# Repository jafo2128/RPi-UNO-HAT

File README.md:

# RPi-UNO-HAT
Raspberry Pi to Arduino/Genuino Shield Bridge.

## Shop
* [RPi-UNO-HAT](http://www.watterott.com/en/RPi-UNO-HAT)

## Features
* Atmel AVR ATmega328 with Arduino compatible Bootloader (optiboot)
* Raspberry Pi connected via I2C and UART (to the AVR through level-shifter)
* AVR-Programming via Raspberry Pi possible
* Shield connectors with Uno R3 layout
* Additional 3.3V LDO voltage regulator for Shields
* Optional 7-36V power input for Raspberry Pi and RPi-UNO-HAT (Murata OKI-78SR-5)

## Hardware and Software
* [Schematics + Layout](https://github.com/watterott/RPi-UNO-HAT/tree/master/hardware)
* [How to install the Arduino IDE on Raspberry Pi](https://github.com/watterott/RPi-UNO-HAT/blob/master/docu/Arduino.md)
* [How to control the RPi-UNO-HAT with Firmata](https://github.com/watterott/RPi-UNO-HAT/blob/master/docu/Firmata.md)
* [How to communicate with the RPi-UNO-HAT via I2C](https://github.com/watterott/RPi-UNO-HAT/blob/master/docu/I2CTest.md)
* [How to flash/update EEPROM on the RPi-UNO-HAT](https://github.com/watterott/RPi-UNO-HAT/blob/master/docu/EEPROM.md)
* [Nuage a Arduino Yún compatible device](http://www.arduino-hausautomation.de/nuage/)

Finally words from us Archivers and Developers.. 

##### Donate

People from time to time wish to donate a little money. Donating won't get you anything special, other than a warm feeling inside, and possibly urge me to produce more freely available material for interesting projects. You can donate via [PayPal](https://www.paypal.com), just click [donate](https://www.paypal.com/cgi-bin/webscr?cmd=_s-xclick&hosted_button_id=3PXVSLXFBS45E) button available below - it will redirect you to the secured PayPal page where you can provide donation amount (there is no minimal value). Any donations are apreciated greatly, and we thank you all in advance for your support along the ways..

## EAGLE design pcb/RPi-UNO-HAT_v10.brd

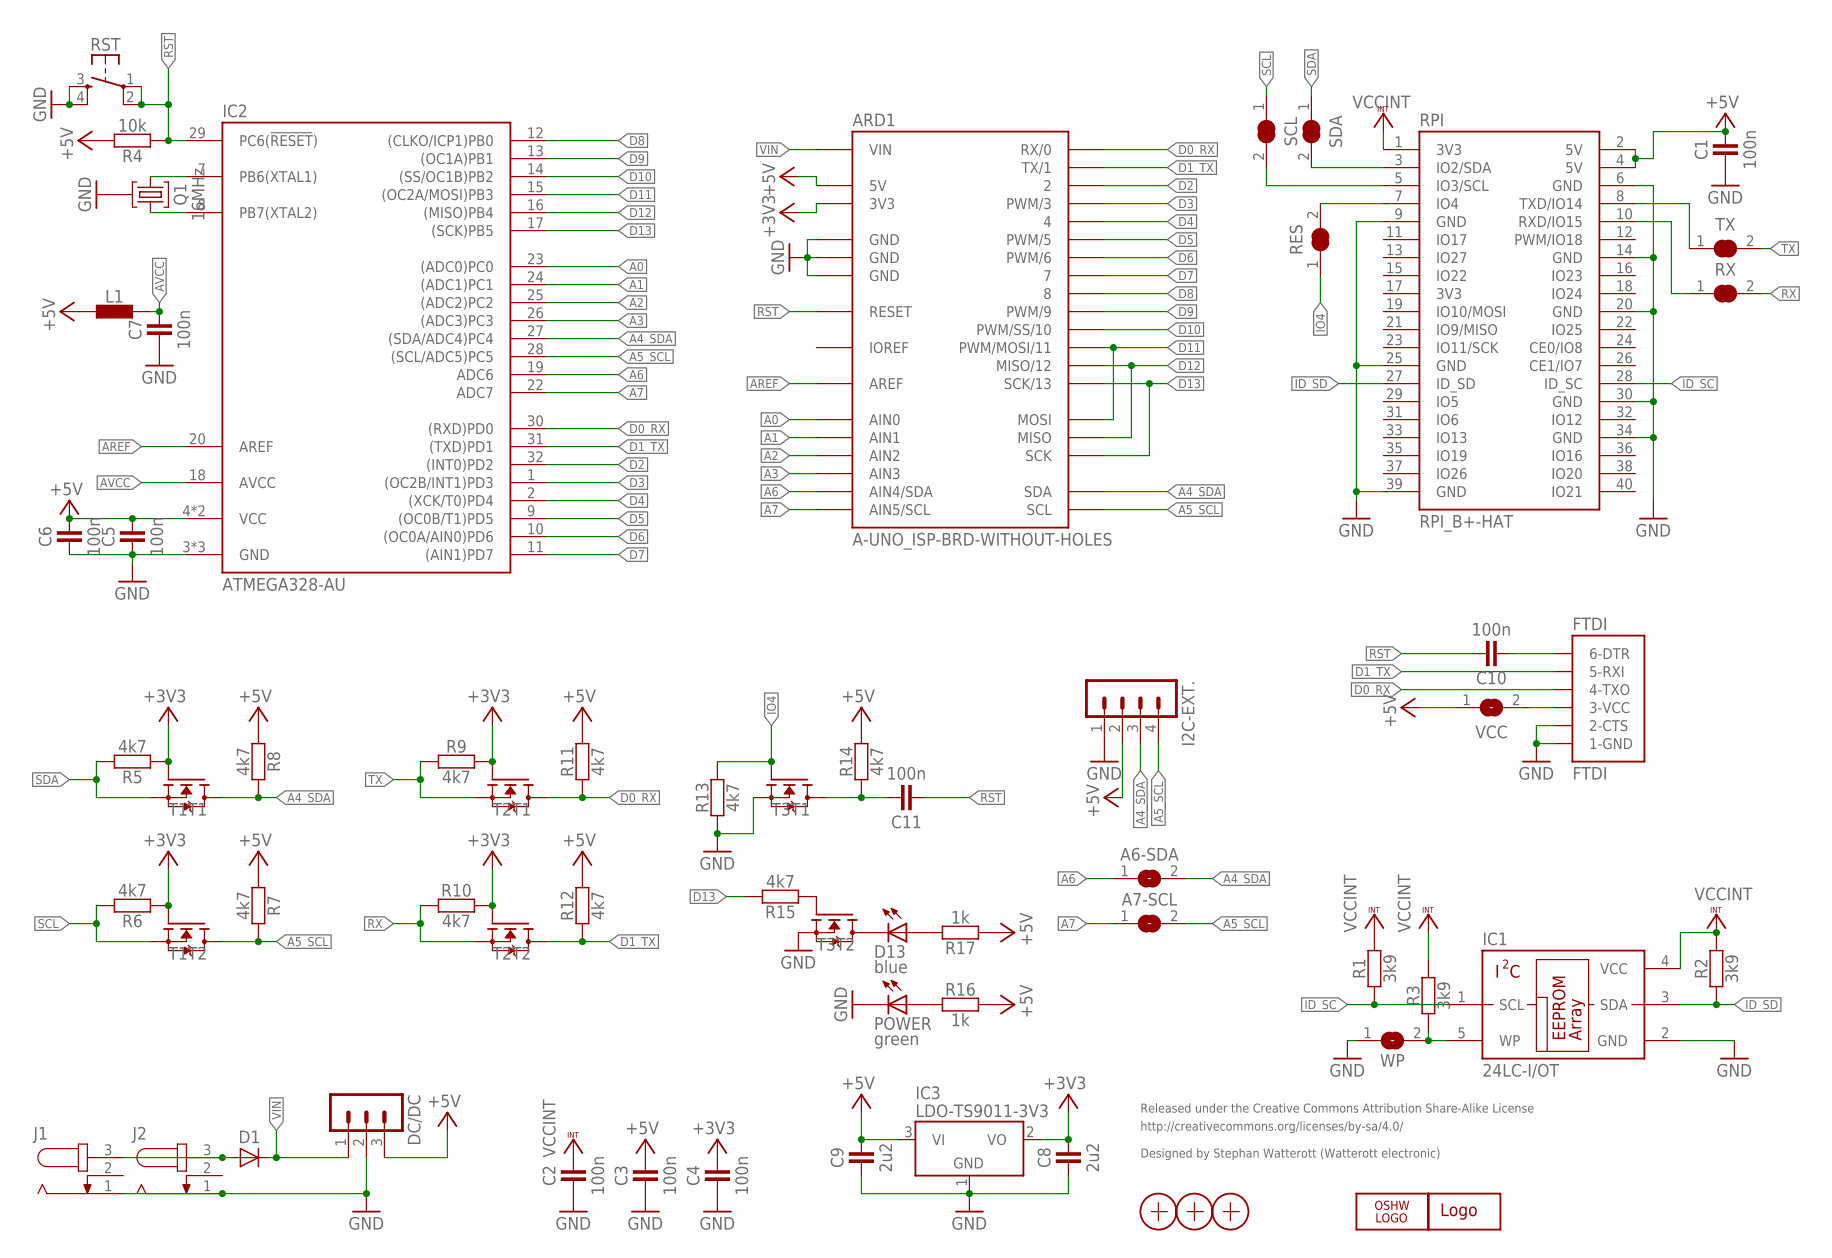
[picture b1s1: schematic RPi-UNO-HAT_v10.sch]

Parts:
A6-SDA, A7-SCL: JUMPER2-0402-NC; JUMPER2-0402_NC
ARD1: A-UNO_ISP-BRD-WITHOUT-HOLES; A-UNO-ISP_CON-WITHOUT-HOLES
C1, C2, C3, C4, C5, C6, C7, C10, C11: 100n; C0402
C8, C9: 2u2; C0402
D1: DIODE-SOD80; SOD80
D13: blue; C0603
DC/DC: MA03-1
FTDI: FTDI
I2C-EXT.: JST_PH_4B4B-PH-SM4-TB; JST_B4B-PH-SM4-TB
IC1: 24LC-I/OT; SOT23-5
IC2: ATMEGA328-AU; TQFP32
IC3: LDO-TS9011-3V3; SOT23
J1, J2: DC-JACK
L1: INDUCTOR-0603; C0603
LOGO1: LOGO-S_PLACE_S; SPARK_TPLACE_S
LOGO2: OSHW_LOGOX0070; OSHW_6X70
POWER: green; C0603
Q1: 16MHz; CRYSTAL_32X13
R1, R2, R3: 3k9; C0402
R4: 10k; C0402
R5, R6, R7, R8, R9, R10, R11, R12, R13, R14, R15: 4k7; C0402
R16, R17: 1k; C0402
RES: JUMPER2-0402-NC; JUMPER2-0402_NC
RPI: RPI_B+-HAT; RPI-B+HAT
RST: SW-TACTILE-PTS840P; SW_PTS840P
RX: JUMPER2-0402-NC; JUMPER2-0402_NC
SCL: JUMPER2-0402-NC; JUMPER2-0402_NC
SDA: JUMPER2-0402-NC; JUMPER2-0402_NC
T1, T2, T3: BSS138PS; SOT363
TX: JUMPER2-0402-NC; JUMPER2-0402_NC
VCC: JUMPER2-0402-NC; JUMPER2-0402_NC
WP: JUMPER2-0603-NC; JUMPER2-0603_NC
X1, X2, X3: PASSER-07; PASSER_07MM

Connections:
+3V3: ARD1.3V3, C4.2, C8.2, IC3.2 (VO), R5.1, R6.1, R9.2, R10.2, T1.2 (G), T1.5 (G), T2.2 (G), T2.5 (G)
+5V: ARD1.5V, ARD1.VCC (5V), C1.2, C3.2, C5.2, C6.2, C9.2, DC/DC.3, I2C-EXT..2, IC2.4 (VCC), IC2.6 (VCC), IC3.3 (VI), L1.1, R4.2, R7.1, R8.1, R11.2, R12.2, R14.2, R16.2, R17.1, RPI.2 (5V), RPI.4 (5V), VCC.1
A0: ARD1.A0 (AIN0), IC2.23 ((ADC0)PC0)
A1: ARD1.A1 (AIN1), IC2.24 ((ADC1)PC1)
A2: ARD1.A2 (AIN2), IC2.25 ((ADC2)PC2)
A3: ARD1.A3 (AIN3), IC2.26 ((ADC3)PC3)
A4_SDA: A6-SDA.2, ARD1.SDA, I2C-EXT..3, IC2.27 ((SDA/ADC4)PC4), R8.2, T1.6 (D)
A5_SCL: A7-SCL.2, ARD1.SCL, I2C-EXT..4, IC2.28 ((SCL/ADC5)PC5), R7.2, T1.3 (D)
A6: A6-SDA.1, ARD1.A4 (AIN4/SDA), IC2.19 (ADC6)
A7: A7-SCL.1, ARD1.A5 (AIN5/SCL), IC2.22 (ADC7)
AREF: ARD1.AREF, IC2.20 (AREF)
AVCC: C7.2, IC2.18 (AVCC), L1.2
D0_RX: ARD1.0 (RX/0), FTDI.4-TX (4-TXO), IC2.30 ((RXD)PD0), R11.1, T2.6 (D)
D0_RX1: C11.2, R14.1, T3.6 (D)
D1_TX: ARD1.1 (TX/1), FTDI.5-RX (5-RXI), IC2.31 ((TXD)PD1), R12.1, T2.3 (D)
D2: ARD1.2, IC2.32 ((INT0)PD2)
D3: ARD1.3 (PWM/3), IC2.1 ((OC2B/INT1)PD3)
D4: ARD1.4, IC2.2 ((XCK/T0)PD4)
D5: ARD1.5 (PWM/5), IC2.9 ((OC0B/T1)PD5)
D6: ARD1.6 (PWM/6), IC2.10 ((OC0A/AIN0)PD6)
D7: ARD1.7, IC2.11 ((AIN1)PD7)
D8: ARD1.8, IC2.12 ((CLKO/ICP1)PB0)
D9: ARD1.9 (PWM/9), IC2.13 ((OC1A)PB1)
D10: ARD1.10 (PWM/SS/10), IC2.14 ((SS/OC1B)PB2)
D11: ARD1.11 (PWM/MOSI/11), ARD1.MOSI, IC2.15 ((OC2A/MOSI)PB3)
D12: ARD1.12 (MISO/12), ARD1.MISO, IC2.16 ((MISO)PB4)
D13: ARD1.13 (SCK/13), ARD1.SCK, IC2.17 ((SCK)PB5), R15.2
GND: ARD1.GND@1 (GND), ARD1.GND@2 (GND), ARD1.GND@3 (GND), ARD1.GND@4 (GND), C1.1, C2.1, C3.1, C4.1, C5.1, C6.1, C7.1, C8.1, C9.1, DC/DC.2, FTDI.1-GND, FTDI.2-CTS, I2C-EXT..1, IC1.2 (GND), IC2.3 (GND), IC2.5 (GND), IC2.21 (GND), IC3.1 (GND), J1.1, J2.1, POWER.C, Q1.GND, R13.1, RPI.6 (GND), RPI.9 (GND), RPI.14 (GND), RPI.20 (GND), RPI.25 (GND), RPI.30 (GND), RPI.34 (GND), RPI.39 (GND), RST.3 (S1), RST.4 (S2), T3.1 (S), T3.4 (S), WP.1
ID_SC: IC1.1 (SCL), R1.1, RPI.28 (ID_SC)
ID_SD: IC1.3 (SDA), R2.1, RPI.27 (ID_SD)
IO4: R13.2, RES.1, T3.2 (G)
IOREF: ARD1.IOREF
unnamed: IC2.8 (PB7(XTAL2)), Q1.1
unnamed: IC2.7 (PB6(XTAL1)), Q1.2
unnamed: D1.A, J1.3, J2.3
unnamed: C10.1, FTDI.6-DTR
unnamed: RPI.8 (TXD/IO14), TX.1
unnamed: RPI.10 (RXD/IO15), RX.1
unnamed: RES.2, RPI.7 (IO4)
unnamed: FTDI.3-VCC, VCC.2
unnamed: RPI.5 (IO3/SCL), SCL.2
unnamed: RPI.3 (IO2/SDA), SDA.2
unnamed: R15.1, T3.5 (G)
unnamed: POWER.A, R16.1
unnamed: D13.A, R17.2
unnamed: D13.C, T3.3 (D)
RST: ARD1.RST (RESET), ARD1.RST2 (RESET), C10.2, C11.1, IC2.29 (PC6(!RESET!)), R4.1, RST.1, RST.2
RX: R10.1, RX.2, T2.4 (S)
SCL: R6.2, SCL.1, T1.4 (S)
SDA: R5.2, SDA.1, T1.1 (S)
TX: R9.1, T2.1 (S), TX.2
VCCINT: C2.2, IC1.4 (VCC), R1.2, R2.2, R3.2, RPI.1 (3V3)
VIN: ARD1.VIN, D1.C, DC/DC.1
WP: IC1.5 (WP), R3.1, WP.2

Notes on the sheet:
Released under the Creative Commons Attribution Share-Alike License
http://creativecommons.org/licenses/by-sa/4.0/
Designed by Stephan Watterott (Watterott electronic)

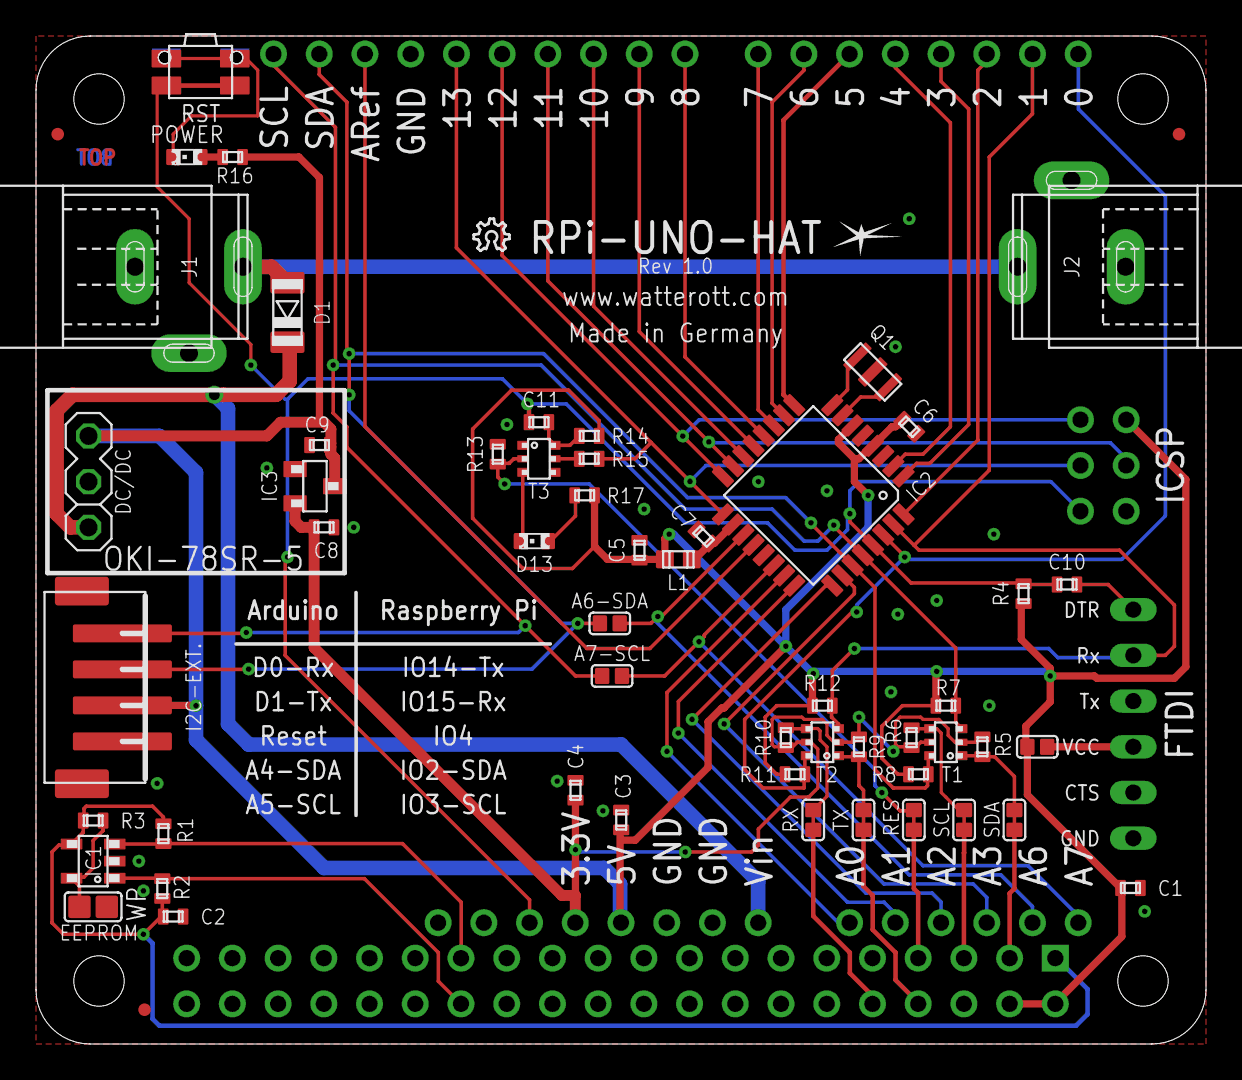
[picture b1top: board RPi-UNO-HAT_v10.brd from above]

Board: 2 copper layers, 65.0 x 56.0 mm, 61 parts (0 on the bottom side), 53 nets.

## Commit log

2015-04-24 updated readme and added image
2015-04-24 added docu and examples
2015-04-24 udpated docu
2015-05-09 added schematics and layout
2015-05-09 updated docu
2015-05-18 updated readme and docu
2015-08-21 changed path structure
2015-09-16 updated autoreset
2015-10-05 updated autoreset (timout bugfix)
2015-12-04 moved info message to the start
